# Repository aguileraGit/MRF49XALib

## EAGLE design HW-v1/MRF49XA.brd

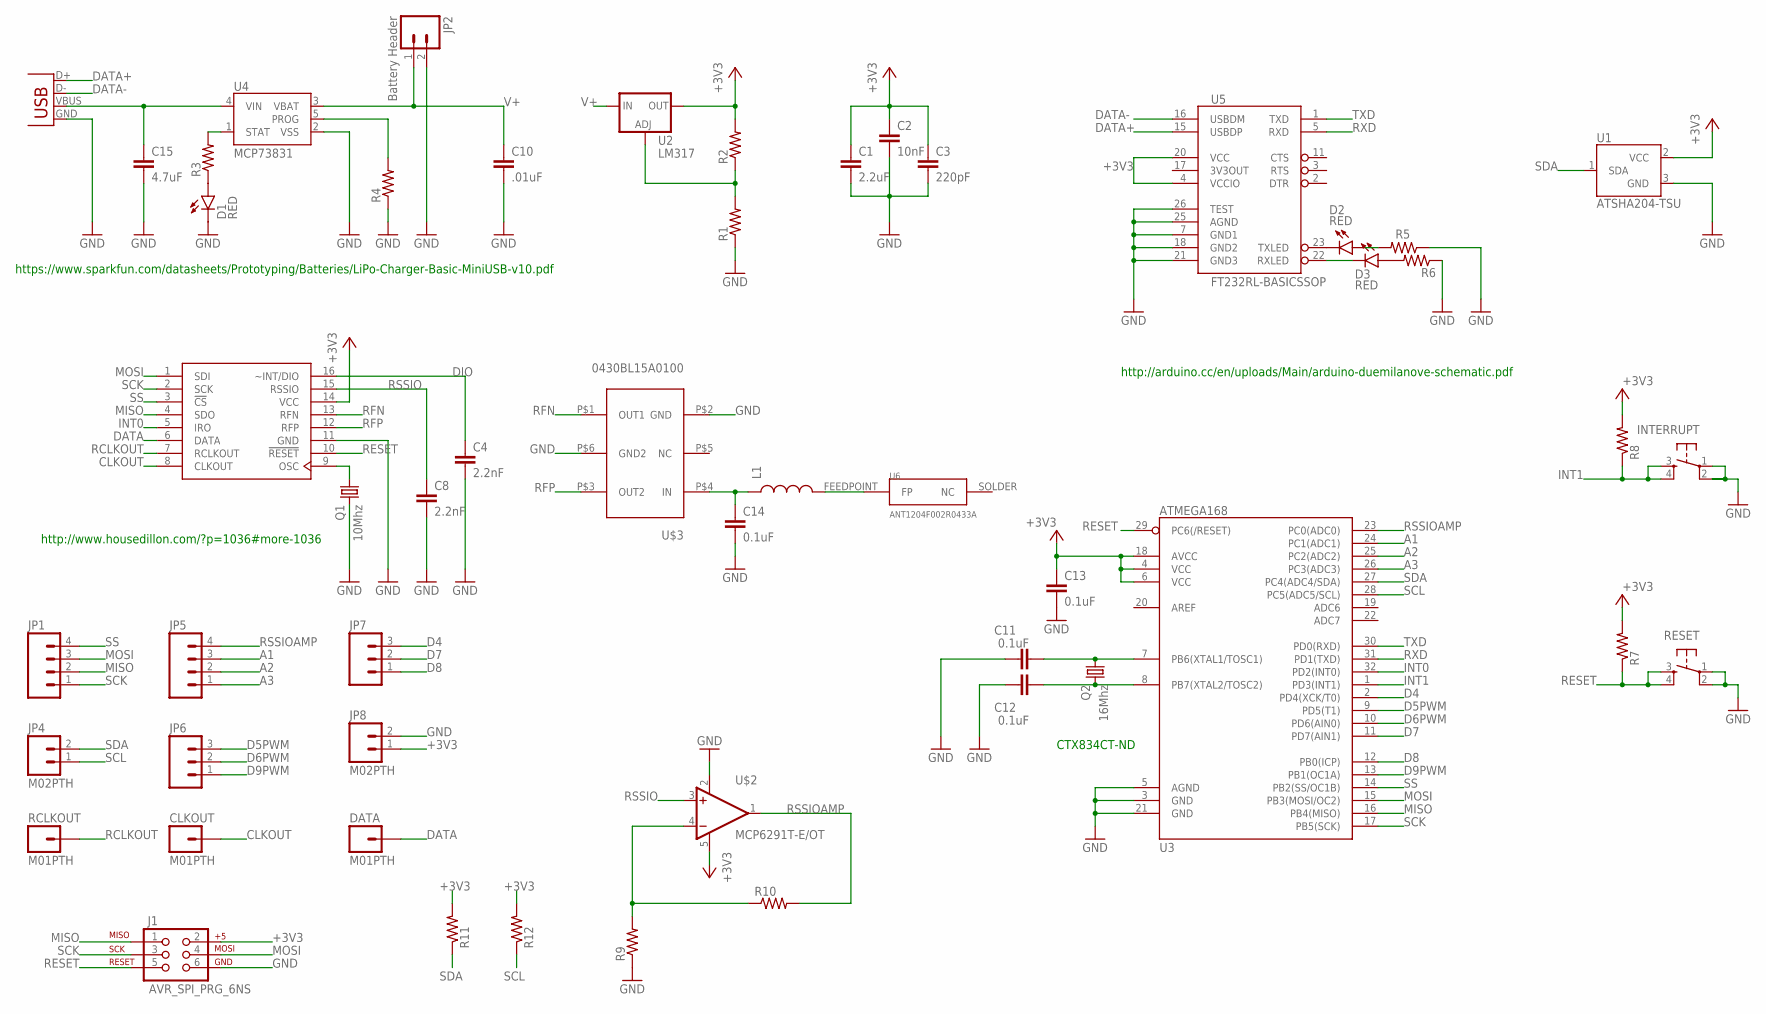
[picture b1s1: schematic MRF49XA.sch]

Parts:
C1: 2.2uF; C3216
C2: 10nF; C0603K
C3: 220pF; C0603
C4, C8: 2.2nF; C0603K
C10: .01uF; C3216
C11, C12, C13, C14: 0.1uF; 0603-CAP
C15: 4.7uF; C3216
CLKOUT: M01PTH; 1X01
D1, D2, D3: RED; LED-0603
DATA: M01PTH; 1X01
INTERRUPT: TAC_SWITCHSMD; TACTILE-SWITCH-SMD
J1: AVR_SPI_PRG_6NS; 2X3-NS
JP1, JP5: M04PTH; 1X04
JP2: Battery Header; 1X02_LOCK_LONGPADS
JP3: USBSMD; USB-MINIB
JP4, JP8: M02PTH; 1X02
JP6, JP7: M03PTH; 1X03
L1: INDUCTOR0603; 0603
Q1: 10Mhz; CTS406
Q2: 16Mhz; CTS406
R1, R2, R5, R6, R7, R8, R11, R12: R-US_R0603; R0603
R3, R4, R9, R10: RESISTOR0603-RES; 0603-RES
RCLKOUT: M01PTH; 1X01
RESET: TAC_SWITCHSMD; TACTILE-SWITCH-SMD
U1: ATSHA204-TSU; SOT23-3
U2: LM317; SOT223
U3: ATMEGA168; TQFP32-08
U4: MCP73831; SOT23-5
U5: FT232RL-BASICSSOP; SSOP28DB
U6: ANT1204F002R0433A
U$1: MRF49XA; TSSOP16
U$2: MCP6291T-E/OT; SOT23-5
U$3: 0430BL15A0100

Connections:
+3V3: C1.1, C2.1, C3.1, C13.1, J1.2, JP8.1, R2.2, R7.2, R8.2, R11.2, R12.2, U1.2 (VCC), U2.2 (OUT), U3.4 (VCC), U3.6 (VCC), U3.18 (AVCC), U5.4 (VCCIO), U5.20 (VCC), U$1.14 (VCC), U$2.5 (V+)
A1: JP5.3, U3.24 (PC1(ADC1))
A2: JP5.2, U3.25 (PC2(ADC2))
A3: JP5.1, U3.26 (PC3(ADC3))
CLKOUT: CLKOUT.1, U$1.8 (CLKOUT)
D4: JP7.3, U3.2 (PD4(XCK/T0))
D5PWM: JP6.3, U3.9 (PD5(T1))
D6PWM: JP6.2, U3.10 (PD6(AIN0))
D7: JP7.2, U3.11 (PD7(AIN1))
D8: JP7.1, U3.12 (PB0(ICP))
D9PWM: JP6.1, U3.13 (PB1(OC1A))
DATA: DATA.1, U$1.6 (DATA)
DATA+: JP3.D+, U5.15 (USBDP)
DATA-: JP3.D-, U5.16 (USBDM)
DIO: C4.1, U$1.16 (~INT/DIO)
GND: C1.2, C2.2, C3.2, C4.2, C8.2, C10.2, C11.1, C12.1, C13.2, C14.2, C15.2, D1.C, INTERRUPT.1, INTERRUPT.2, J1.6, JP2.2, JP3.GND, JP8.2, Q1.3 (2), R1.1, R4.1, R5.1, R6.1, R9.1, RESET.1, RESET.2, U1.3 (GND), U3.3 (GND), U3.5 (AGND), U3.21 (GND), U4.2 (VSS), U5.7 (GND1), U5.18 (GND2), U5.21 (GND3), U5.25 (AGND), U5.26 (TEST), U$1.11 (GND), U$2.2 (V-), U$3.P$2 (GND), U$3.P$6 (GND2)
INT0: U3.32 (PD2(INT0)), U$1.5 (IRO)
INT1: INTERRUPT.3, INTERRUPT.4, R8.1, U3.1 (PD3(INT1))
MISO: J1.1, JP1.2, U3.16 (PB4(MISO)), U$1.4 (SDO)
MOSI: J1.4, JP1.3, U3.15 (PB3(MOSI/OC2)), U$1.1 (SDI)
unnamed: Q1.1, U$1.9 (OSC)
unnamed: L1.2, U6.FEEDPOINT (FP)
unnamed: C15.1, JP3.VBUS, U4.4 (VIN)
unnamed: R3.2, U4.1 (STAT)
unnamed: D1.A, R3.1
unnamed: R4.2, U4.5 (PROG)
unnamed: D2.C, U5.23 (TXLED)
unnamed: D3.C, U5.22 (RXLED)
unnamed: D2.A, R5.2
unnamed: D3.A, R6.2
unnamed: C11.2, Q2.1, U3.7 (PB6(XTAL1/TOSC1))
unnamed: C12.2, Q2.3 (2), U3.8 (PB7(XTAL2/TOSC2))
unnamed: R9.2, R10.1, U$2.4 (-IN)
unnamed: R1.2, R2.1, U2.1 (ADJ)
unnamed: C14.1, L1.1, U$3.P$4 (IN)
RCLKOUT: RCLKOUT.1, U$1.7 (RCLKOUT)
RESET: J1.5, R7.1, RESET.3, RESET.4, U3.29 (PC6(/RESET)), U$1.10 (!RESET)
RFN: U$1.13 (RFN), U$3.P$1 (OUT1)
RFP: U$1.12 (RFP), U$3.P$3 (OUT2)
RSSIO: C8.1, U$1.15 (RSSIO), U$2.3 (+IN)
RSSIOAMP: JP5.4, R10.2, U3.23 (PC0(ADC0)), U$2.1 (OUT)
RXD: U3.31 (PD1(TXD)), U5.5 (RXD)
SCK: J1.3, JP1.1, U3.17 (PB5(SCK)), U$1.2 (SCK)
SCL: JP4.1, R12.1, U3.28 (PC5(ADC5/SCL))
SDA: JP4.2, R11.1, U1.1 (SDA), U3.27 (PC4(ADC4/SDA))
SS: JP1.4, U3.14 (PB2(SS/OC1B)), U$1.3 (!CS)
TXD: U3.30 (PD0(RXD)), U5.1 (TXD)
V+: C10.1, JP2.1, U2.3 (IN), U4.3 (VBAT)
VSS: U$1.P$1 (VSS)

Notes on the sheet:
CTX834CT-ND
https://www.sparkfun.com/datasheets/Prototyping/Batteries/LiPo-Charger-Basic-MiniUSB-v10.pdf
http://arduino.cc/en/uploads/Main/arduino-duemilanove-schematic.pdf
http://www.housedillon.com/?p=1036#more-1036

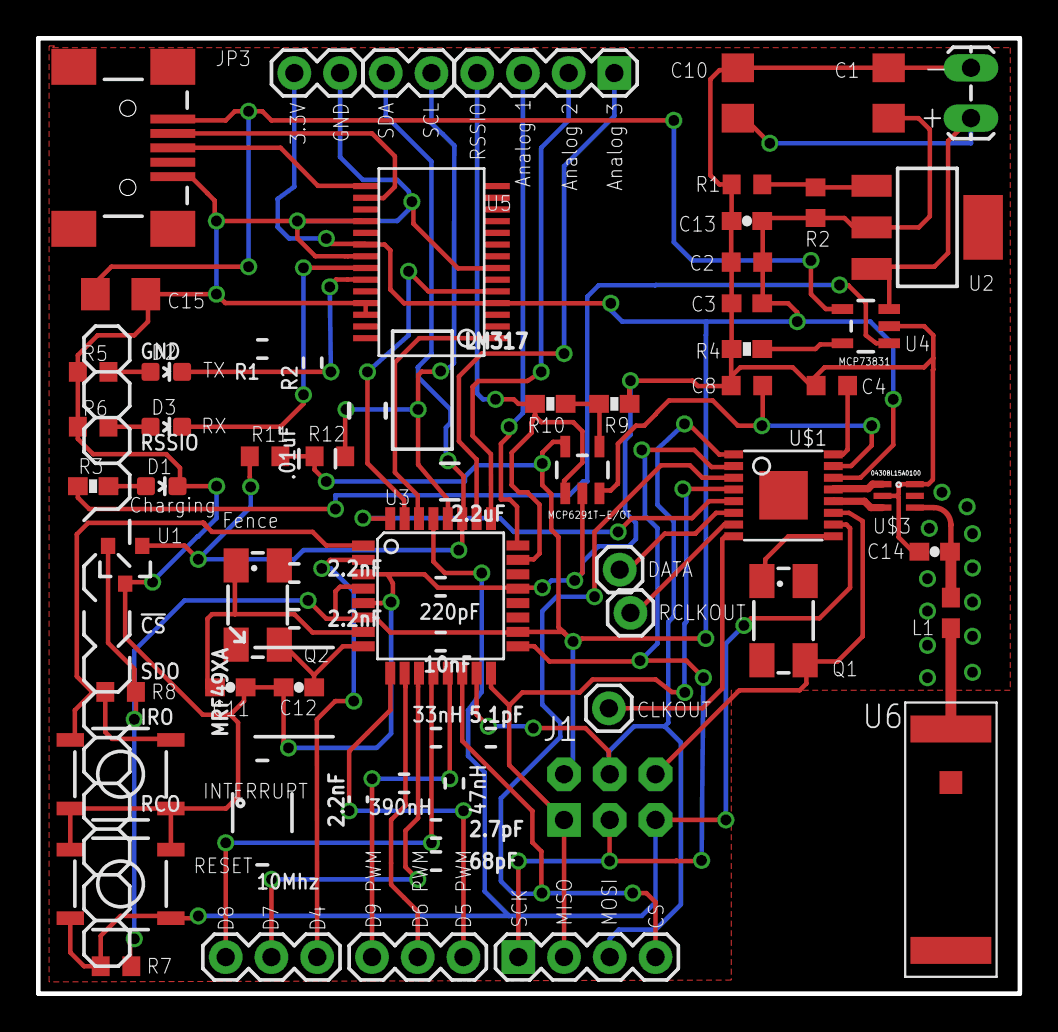
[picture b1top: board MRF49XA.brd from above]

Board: 2 copper layers, 54.5 x 53.1 mm, 52 parts (0 on the bottom side), 48 nets.

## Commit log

2014-09-16 MRF49XA Library
    Library for Microchip MRF49XA IC.
2014-09-16 Adding schematics
    v1
2014-09-16 Add schematics and layout

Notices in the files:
HW-v1/MRF49XA.brd:
(C) 2010 - William Dillon KD7VMY
Licensed under the
TAPR Open Hardware License
parts and their libraries:
SparkFun-DigitalIC: Licensing: Creative Commons ShareAlike 4.0 International - https://creativecommons.org/licenses/by-sa/4.0
